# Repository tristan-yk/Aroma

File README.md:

# Aroma Control Board

**Aroma Controller** is a compact ESP32 project that drives a multi‑scent diffuser with an intuitive on‑device UI. A five‑way joystick selects between an **OFF** state and several active scent profiles, while a small SPI TFT displays the current mode and status. The goal is a clean, responsive interface that runs untethered and can be extended with timers or profiles.

The firmware uses a debounced state machine so each joystick action cleanly toggles its corresponding scent. A simple analog water‑level input is monitored and shown on screen to avoid running dry. The display presents a title view and per‑scent screens with distinct themes, and draw calls are kept lightweight to minimize tearing on the SPI bus.

The board is powered and programmed over **USB‑C** for easy access, with programming handled by an onboard **USB‑to‑UART** converter. An onboard **boost converter** generates 12 V to drive **five pump channels** (five total scents), and a **5 V fan** automatically runs whenever any pump is active. The board also integrates the analog water sensor, debounced joystick input, and a color SPI TFT (ST7789, 1.9″ 320×170).

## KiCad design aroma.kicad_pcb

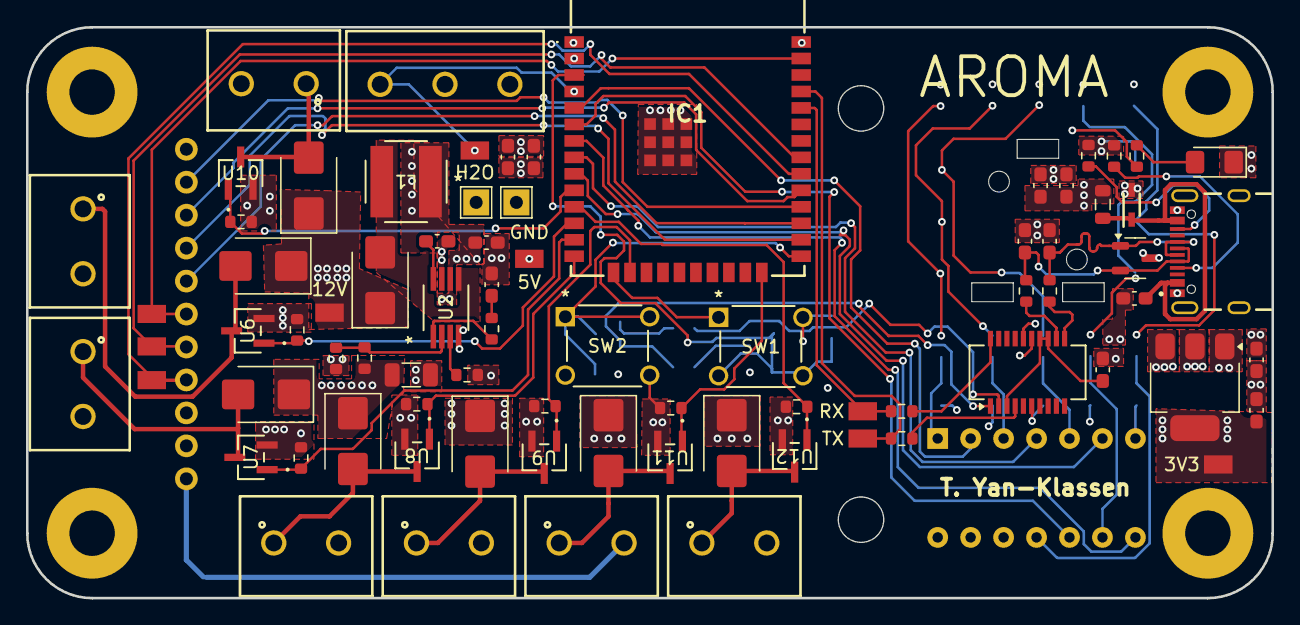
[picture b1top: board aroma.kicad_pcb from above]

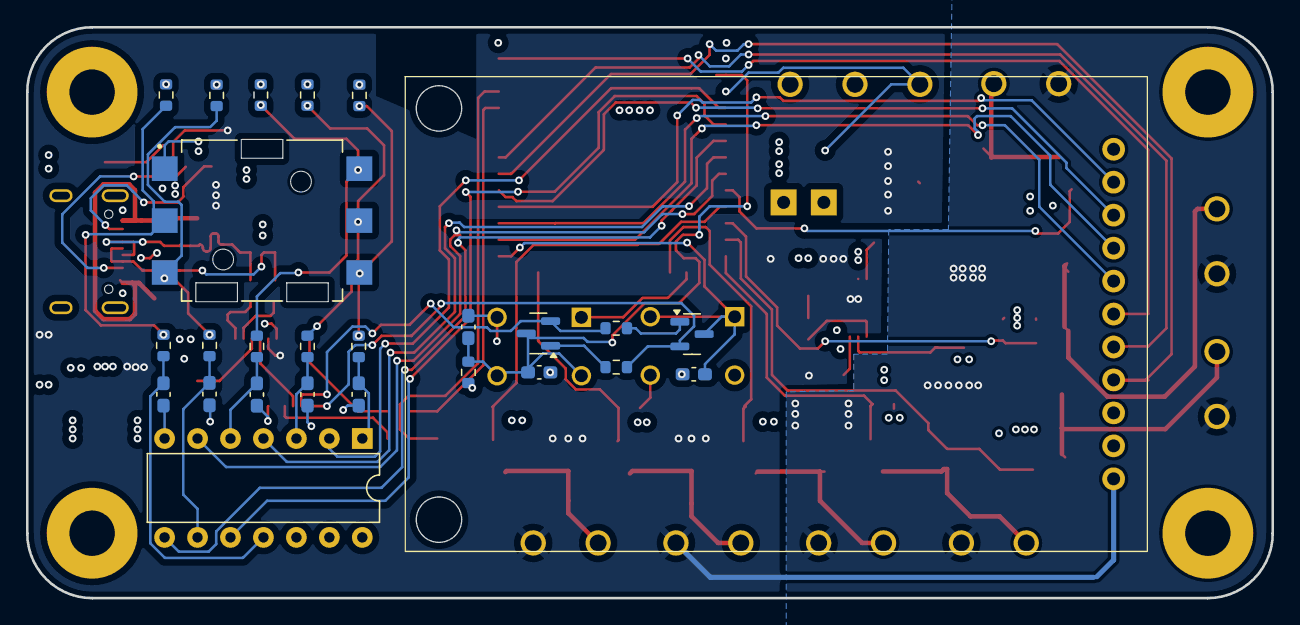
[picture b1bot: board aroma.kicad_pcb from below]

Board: 4 copper layers, 96.0 x 44.0 mm, 108 parts (26 on the bottom side), 66 nets.

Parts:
3V3, 5V, 12V: S2751-46R
C1, C2, C3, C5, C7, C11, C18, C19, C20, C21, C22: 100n; C_0603_1608Metric_Pad1.08x0.95mm_HandSolder
C4: 1u; C_0603_1608Metric_Pad1.08x0.95mm_HandSolder
C6: 10n; C_0603_1608Metric_Pad1.08x0.95mm_HandSolder
C8: 4u7; C_0603_1608Metric_Pad1.08x0.95mm_HandSolder
C9, C10: 47p; C_0603_1608Metric_Pad1.08x0.95mm_HandSolder
C12: 10u; C_0603_1608Metric_Pad1.08x0.95mm_HandSolder
C13: 33n; C_0603_1608Metric_Pad1.08x0.95mm_HandSolder
C14: 1n8; C_0603_1608Metric_Pad1.08x0.95mm_HandSolder
C15: 10u; C_1206_3216Metric
C16, C17: 22u; C_0603_1608Metric_Pad1.08x0.95mm_HandSolder
D1: LED; LED_1206_3216Metric_Pad1.42x1.75mm_HandSolder
D2: ESD5V0D3-TP
D3: SOT-23-3
D4, D5, D6, D7, D8, D9, D10, D11: B260; D_SMB
FB1: FerriteBead; L_0805_2012Metric
GND: TestPoint; TestPoint_THTPad_2.0x2.0mm_Drill1.0mm
H1, H2, H3, H4: MountingHole_Pad; MountingHole_3.5mm_Pad
H2O: S2751-46R
IC1: ESP32-WROOM-32E-N8R2; ESP32WROOM32EN8R2
J1: USB4105-GF-A; GCT_USB4105-GF-A
J2: 691137710003
J3, J4, J5, J6, J7, J8, J9: 691137710002
L1: 10u; IND_NP-100NC_SUM
Q1, Q2: SS8050; SOT-23
R1, R7, R8, R11, R13, R15, R16, R17, R18, R19, R20, R21, R22, R23, R24, R25, R26, R27, R28, R29, R30, R31: 10k; R_0603_1608Metric
R2: 150R; R_0603_1608Metric
R3, R4: 5k1; R_0603_1608Metric
R5, R6: 27R; R_0603_1608Metric
R9, R10: 0R; R_0603_1608Metric
R12: 86k6; R_0603_1608Metric
R14: 22k; R_0603_1608Metric
RX: S2751-46R
SW1, SW2: 1825910-6; SW4_1825910-B_TEC
SW3: JS5208; SW_JS5208
TP1: TestPoint; TestPoint_THTPad_2.0x2.0mm_Drill1.0mm
TP6, TP7, TP8: S2751-46R
TX: S2751-46R
U1: FT231XS; SSOP-20_3.9x8.7mm_P0.635mm
U2: ADP1613ARMZ-R7; boost
U3: AMS1117-3.3; SOT-223-3_TabPin2
U4: 74HC14; DIP-14_W7.62mm
U5: LCD_ST7789
U6, U7, U8, U9, U10, U11, U12: BSR802NL6327HTSA1; mosfet

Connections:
+3V3: 3V3.1, C2.1, C4.1, C17.1, IC1.2 (3V3), J2.2, R1.1, R16.1, R18.1, R19.1, R21.1, R23.1, U3.2 (VO), U4.14 (VCC)
+5V: 5V.1, C7.1, C8.1, C12.1, C16.1, D10.1 (K), D11.1 (K), FB1.2, J8.2, J9.2, L1.1, R2.1, R11.1, U1.15 (VCC), U2.6 (VIN), U3.3 (VI), U5.1 (Vin)
+12V: 12V.1, C15.1, D4.1 (K), D5.1 (K), D6.1 (K), D7.1 (K), D8.1 (K), D9.1 (K), J3.2, J4.2, J5.2, J6.2, J7.2, R12.1
/Diffuser/MIST: IC1.11 (IO26), R31.1, U12.1
/Externals/A: IC1.5 (SENSOR_VN), U4.2
/Externals/B: IC1.6 (IO34), U4.10
/Externals/C: IC1.9 (IO33), U4.6
/Externals/D: IC1.8 (IO32), U4.4
/Externals/E: IC1.7 (IO35), U4.8
/Externals/H2O: H2O.1, IC1.4 (SENSOR_VP), J2.3
/FAN/FAN: IC1.24 (IO2), R30.1, U11.1
/FET1/FET: IC1.12 (IO27), R25.1, U6.1
/FET2/FET: IC1.13 (IO14), R26.1, U7.1
/FET3/FET: IC1.14 (IO12), R27.1, U8.1
/FET4/FET: IC1.16 (IO13), R28.1, U9.1
/FET5/FET: IC1.10 (IO25), R29.1, U10.1
/LCD Display/DC: IC1.29 (IO5), U5.9 (DC)
/LCD Display/MISO: IC1.31 (IO19), TP7.1, U5.5 (MISO)
/LCD Display/MOSI: IC1.37 (IO23), TP6.1, U5.6 (MOSI)
/LCD Display/RST: IC1.26 (IO4), U5.8 (RST)
/LCD Display/SCK: IC1.30 (IO18), TP8.1, U5.4 (SCK)
/LCD Display/SDCS: IC1.28 (IO17), U5.10 (SDCS)
/LCD Display/TCS: IC1.27 (IO16), U5.7 (TCS)
/MCU/IO0: C5.2, IC1.25 (IO0), Q2.3 (C), SW2.1, SW2.2
/MCU/MCU_EN: C1.2, C3.1, IC1.3 (EN), Q1.3 (C), R1.2, SW1.3, SW1.4
/MCU/RXD0: IC1.34 (RXD0), R9.2, RX.1
/MCU/TXD0: IC1.35 (TXD0), R10.2, TX.1
/USB and UART/DTR: Q2.2 (E), R7.1, U1.1 (~DTR)
/USB and UART/RTS: Q1.2 (E), R8.1, U1.2 (~RTS)
/USB and UART/USBD+: C10.1, D3.1 (I1), J1.A6 (DP1), J1.B6 (DP2), R6.1
/USB and UART/USBD-: C9.1, D3.2 (I2), J1.A7 (DN1), J1.B7 (DN2), R5.1
GND: C1.1, C2.2, C3.2, C4.2, C5.1, C6.2, C7.2, C8.2, C9.2, C10.2, C11.2, C12.2, C13.2, C14.2, C15.2, C16.2, C17.2, C18.2, C19.2, C20.2, C21.2, C22.2, D1.1 (K), D2.2 (A), D3.3 (GND), GND.1, H1.1, H2.1, H3.1, H4.1, IC1.1 (GND_1), IC1.15 (GND_2), IC1.38 (GND_3), IC1.39 (GND_4), IC1.40 (GND_5), IC1.41 (GND_6), IC1.42 (GND_7), IC1.43 (GND_8), IC1.44 (GND_9), IC1.45 (GND_10), IC1.46 (GND_11), IC1.47 (GND_12), J1.A1_B12 (GND), J1.B1_A12 (GND), J2.1, R3.2, R4.2, R13.2, R25.2, R26.2, R27.2, R28.2, R29.2, R30.2, R31.2, SW1.1, SW1.2, SW2.3, SW2.4, SW3.1 (COMM), TP1.1, U1.6 (GND), U1.16 (GND), U2.4 (GND), U2.7 (FREQ), U3.1 (GND), U4.7 (GND), U5.3 (GND), U6.2, U7.2, U8.2, U9.2, U10.2, U11.2, U12.2
unnamed: C14.1, R14.2
unnamed: C18.1, R15.1, U4.9
unnamed: C19.1, R17.1, U4.11
unnamed: C20.1, R20.1, U4.1
unnamed: C21.1, R22.1, U4.3
unnamed: C22.1, R24.1, U4.5
unnamed: D1.2 (A), R2.2
unnamed: C6.1, D2.1 (K), FB1.1, J1.A4_B9 (VBUS), J1.B4_A9 (VBUS)
unnamed: D4.2 (A), L1.2, U2.5 (SW)
unnamed: D5.2 (A), J3.1, U6.3
unnamed: D6.2 (A), J4.1, U7.3
unnamed: D7.2 (A), J5.1, U8.3
unnamed: D8.2 (A), J6.1, U9.3
unnamed: D9.2 (A), J7.1, U10.3
unnamed: D10.2 (A), J8.1, U11.3
unnamed: D11.2 (A), J9.1, U12.3
unnamed: J1.A5 (CC1), R3.1
unnamed: J1.B5 (CC2), R4.1
unnamed: Q1.1 (B), R7.2
unnamed: Q2.1 (B), R8.2
unnamed: R17.2, R18.2, SW3.2
unnamed: R19.2, R20.2, SW3.6
unnamed: R21.2, R22.2, SW3.5
unnamed: R23.2, R24.2, SW3.4
unnamed: R15.2, R16.2, SW3.3 (PUSH_(N.O.))
unnamed: C11.1, U1.3 (VCCIO), U1.13 (3V3OUT), U1.14 (~RESET)
unnamed: R10.1, U1.4 (RXD)
unnamed: R9.1, U1.20 (TXD)
unnamed: R5.2, U1.12 (USBDM)
unnamed: R6.2, U1.11 (USBDP)
unnamed: R14.1, U2.1 (COMP)
unnamed: R11.2, U2.3 (EN)
unnamed: R12.2, R13.1, U2.2 (FB)
unnamed: C13.1, U2.8 (SS)

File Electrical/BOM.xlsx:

Id | Designator | Footprint | Quantity | Designation | Supplier and ref
1 | U12,U11,U7,U9,U10,U8,U6 | mosfet | 7 | BSR802NL6327HTSA1
2 | J2 | 691137710003 | 1 | 691137710003
3 | TP6,TX,5V,RX,TP8,12V,TP7,H2O,3V3 | S2751-46R | 9 | S2751-46R
4 | R5,R6 | R_0603_1608Metric | 2 | 27R
5 | J8,J9,J6,J7,J4,J5,J3 | 691137710002 | 7 | 691137710002
6 | D1 | LED_1206_3216Metric_Pad1.42x1.75mm_HandSolder | 1 | LED
7 | C17,C16 | C_0603_1608Metric_Pad1.08x0.95mm_HandSolder | 2 | 22u
8 | R26,R31,R28,R27,R11,R30,R13,R25,R29,R1,R24,R17,R15,R20,R8,R21,R16,R22,R23,R19,R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 | R_0603_1608Metric | 22 | 10k
9 | D7,D6,D4,D9,D8,D11,D10,D5 | D_SMB | 8 | B260 | t
10 | SW1,SW2 | SW4_1825910-B_TEC | 2 | 1825910-6 | t
11 | D3 | SOT-23-3 | 1 | ~ | t
12 | L1 | IND_NP-100NC_SUM | 1 | 10u
13 | R9,R10 | R_0603_1608Metric | 2 | 0R
14 | C10,C9 | C_0603_1608Metric_Pad1.08x0.95mm_HandSolder | 2 | 47p
15 | IC1 | ESP32WROOM32EN8R2 | 1 | ESP32-WROOM-32E-N8R2 | t
16 | C8 | C_0603_1608Metric_Pad1.08x0.95mm_HandSolder | 1 | 4u7
17 | R12 | R_0603_1608Metric | 1 | 86k6
18 | C14 | C_0603_1608Metric_Pad1.08x0.95mm_HandSolder | 1 | 1n8
19 | U2 | boost | 1 | ADP1613ARMZ-R7 | t
20 | C15 | C_1206_3216Metric | 1 | 10u
21 | FB1 | L_0805_2012Metric | 1 | FerriteBead | t
22 | C2,C7,C11,C5,C22,C1,C19,C20,C18,C3,C21 | C_0603_1608Metric_Pad1.08x0.95mm_HandSolder | 11 | 100n
23 | R2 | R_0603_1608Metric | 1 | 150R
24 | GND,TP1 | TestPoint_THTPad_2.0x2.0mm_Drill1.0mm | 2 | TestPoint
25 | C6 | C_0603_1608Metric_Pad1.08x0.95mm_HandSolder | 1 | 10n
26 | C4 | C_0603_1608Metric_Pad1.08x0.95mm_HandSolder | 1 | 1u
27 | D2 | ESD5V0D3-TP | 1 | ESD5V0D3-TP | t
28 | U3 | SOT-223-3_TabPin2 | 1 | AMS1117-3.3 | t
29 | R4,R3 | R_0603_1608Metric | 2 | 5k1
30 | J1 | GCT_USB4105-GF-A | 1 | USB4105-GF-A
31 | C13 | C_0603_1608Metric_Pad1.08x0.95mm_HandSolder | 1 | 33n
32 | U1 | SSOP-20_3.9x8.7mm_P0.635mm | 1 | FT231XS | t
33 | R14 | R_0603_1608Metric | 1 | 22k
34 | C12 | C_0603_1608Metric_Pad1.08x0.95mm_HandSolder | 1 | 10u
35 | SW3 | SW_JS5208 | 1 | JS5208 | t
36 | Q2,Q1 | SOT-23 | 2 | SS8050 | t
37 | U5 | LCD_ST7789 | 1 | ~ | t
38 | U4 | DIP-14_W7.62mm | 1 | 74HC14 | t

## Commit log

2025-05-20 gitignore
2025-05-20 LCD Display
2025-05-30 passed drc (somehow)
    board routing is def cooked
    verify:
    - boost layout
    - usb terminal layout
2025-05-31 impedance matching
2025-05-31 fix prelims
2025-05-31 gerber
2025-05-31 gerber fix
2025-07-22 reformatting
2025-07-22 pump selection code
2025-07-23 Integrated LCD Display
2025-07-24 gitignore fix
2025-07-27 README
